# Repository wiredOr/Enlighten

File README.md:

# Arduino library to work with shift register-programmable LED lamps

## Supported LED lamps

* [PL9823](http://www.led-genial.de/mediafiles//Sonstiges/PL9823.pdf)
* [WS2812B](https://www.adafruit.com/datasheets/WS2812B.pdf)

## Build system requirements

* [Arduino](https://www.arduino.cc/en/Main/Software) (tested with v1.6.7)

## Reference

* [Arduino IDE 1.5: Library specification](https://github.com/arduino/Arduino/wiki/Arduino-IDE-1.5:-Library-specification)

## License

MIT style. See [here](./LICENSE).

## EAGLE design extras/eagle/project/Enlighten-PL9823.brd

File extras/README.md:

# Extras

Put documentation or other items to be bundled with the library here.

## CadSoft Eagle project

The folder "eagle" contains schematics, library and board files for the required hardware components, as well as ZIP archives containing pre-created Gerber files.

## Timing

The file "timing.txt" contains electrical and timing data, based on the datasheets of the PL9823 and WS2812-B shift register-programmable LED lamps.

## Bluetooth

This project uses the HC-05 Bluetooth module from Guangzhou HC Information Technology Co., Ltd., mounted on the so-called "gomcu" baseplate ("gomcu CZ-HC-05"). The folder "bluetooth" contains documentation about the HC-05 Bluetooth module.

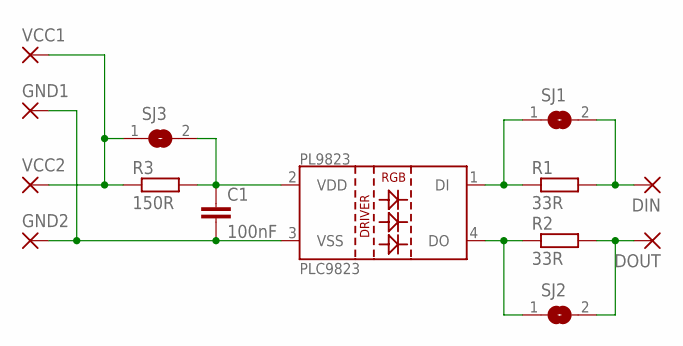
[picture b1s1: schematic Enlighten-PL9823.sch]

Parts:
C1: 100nF; C025-024X044
DIN: SMD2; SMD1,27-2,54
DOUT: SMD2; SMD1,27-2,54
GND1, GND2: SMD5; SMD2,54-5,08
PLC9823: LED-PL9823-F5W
R1, R2: 33R; 0207/10
R3: 150R; 0207/10
SJ1, SJ2, SJ3: SJ
VCC1, VCC2: SMD5; SMD2,54-5,08

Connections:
GND: C1.2, GND1.1, GND2.1, PLC9823.3 (VSS)
unnamed: PLC9823.1 (DI), R1.1, SJ1.1
unnamed: PLC9823.4 (DO), R2.1, SJ2.1
unnamed: DIN.1, R1.2, SJ1.2
unnamed: DOUT.1, R2.2, SJ2.2
unnamed: C1.1, PLC9823.2 (VDD), R3.2, SJ3.2
VCC: R3.1, SJ3.1, VCC1.1, VCC2.1

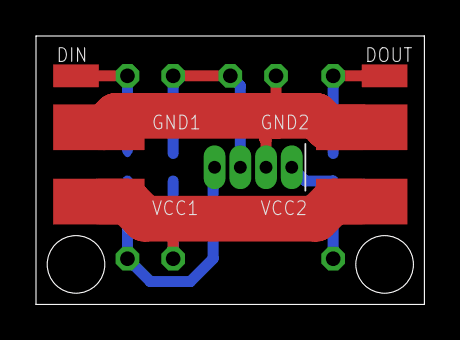
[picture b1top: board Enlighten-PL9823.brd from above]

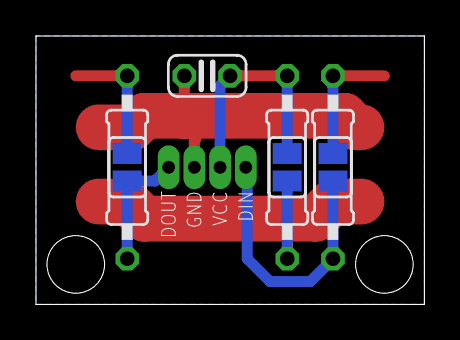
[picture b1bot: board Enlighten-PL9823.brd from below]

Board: 2 copper layers, 21.6 x 14.9 mm, 14 parts (7 on the bottom side), 7 nets.

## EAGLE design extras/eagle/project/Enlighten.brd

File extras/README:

Put documentation or other items to be bundled with the library here.

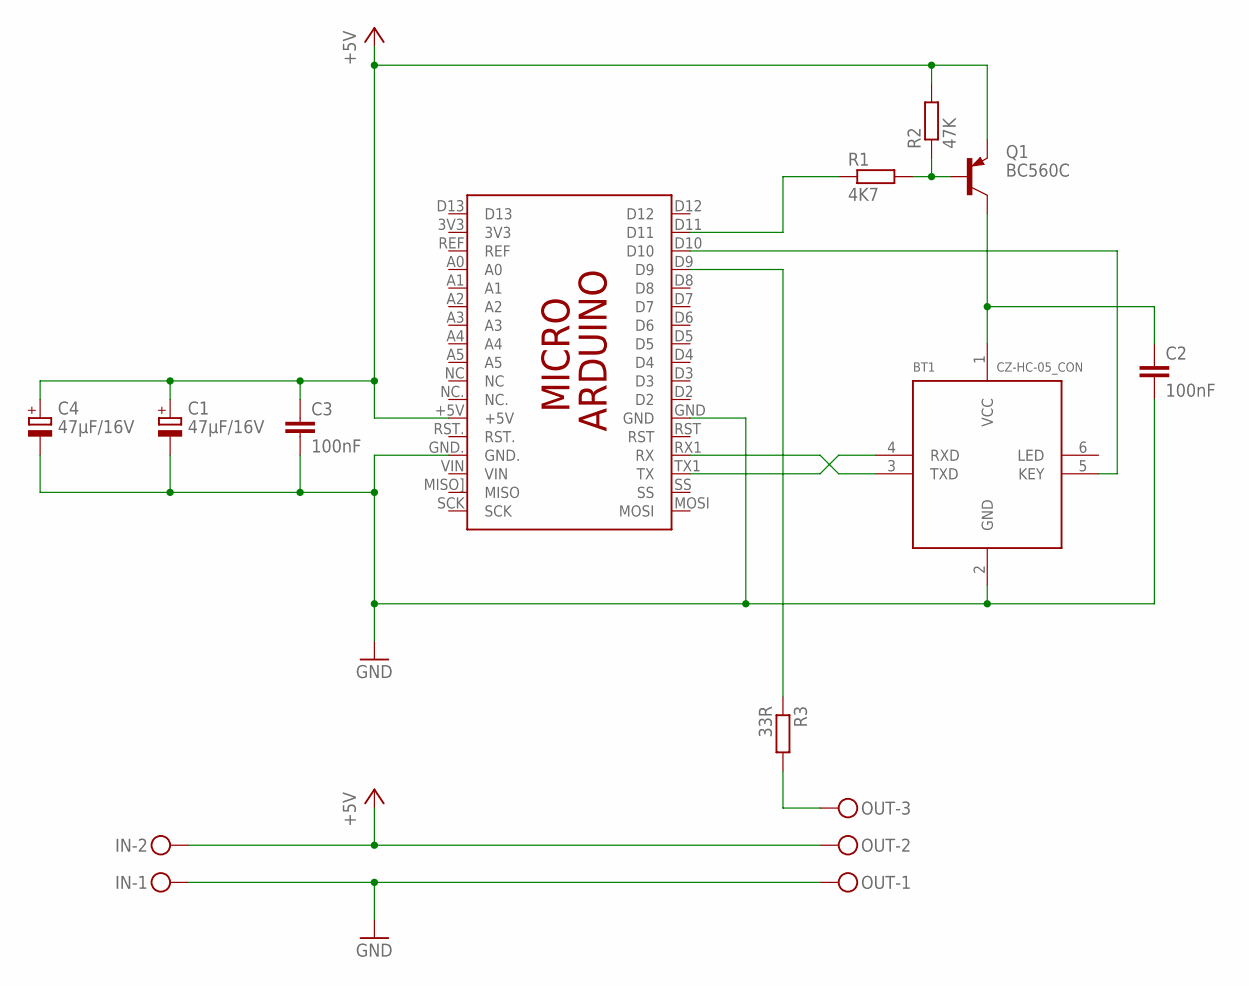
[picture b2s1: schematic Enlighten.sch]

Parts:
BT1: CZ-HC-05_CON
C1, C4: 47µF/16V; E2-5
C2, C3: 100nF; C050-024X044
IN: MKDSN1,5/2-5,08
OUT: MKDSN1,5/3-5,08
PCB1: ARDUINO_MICRO
Q1: BC560C; TO92-EBC
R1: 4K7; 0207/10
R2: 47K; 0207/10
R3: 33R; 0207/10

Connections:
+5V: C1.+, C3.1, C4.+, IN.2, OUT.2, PCB1.+5V, Q1.E, R2.2
BT_KEY: BT1.5 (KEY), PCB1.D10
BT_POWER: PCB1.D11, R1.1
BT_RX: BT1.4 (RXD), PCB1.TX1 (TX)
BT_TX: BT1.3 (TXD), PCB1.RX1 (RX)
DATA: OUT.3, R3.2
GND: BT1.2 (GND), C1.-, C2.2, C3.2, C4.-, IN.1, OUT.1, PCB1.GND, PCB1.GND.
unnamed: BT1.1 (VCC), C2.1, Q1.C
unnamed: Q1.B, R1.2, R2.1
unnamed: PCB1.D9, R3.1

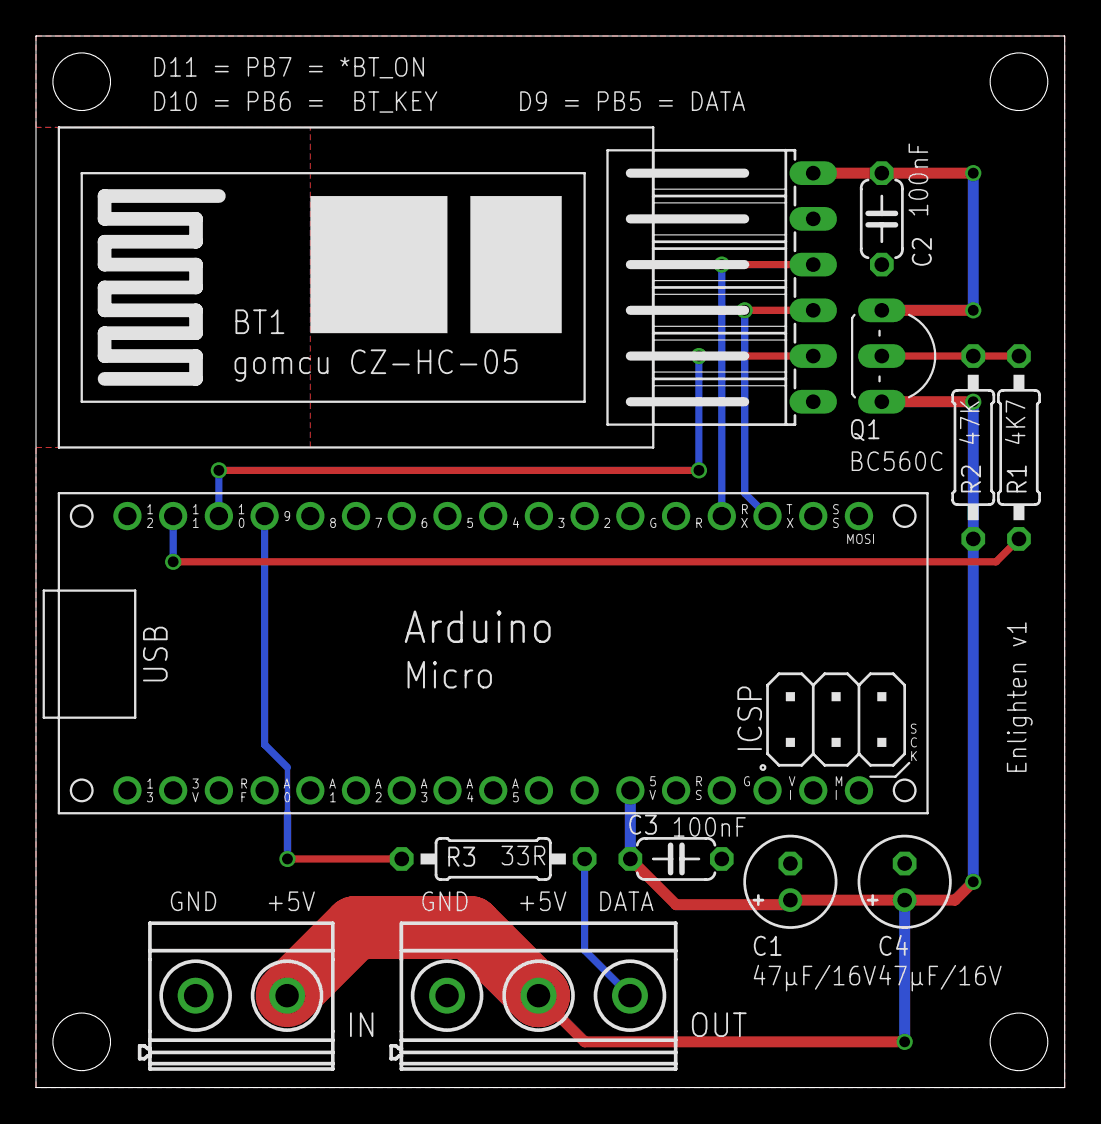
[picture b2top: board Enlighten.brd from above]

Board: 2 copper layers, 57.1 x 58.4 mm, 12 parts (0 on the bottom side), 10 nets.

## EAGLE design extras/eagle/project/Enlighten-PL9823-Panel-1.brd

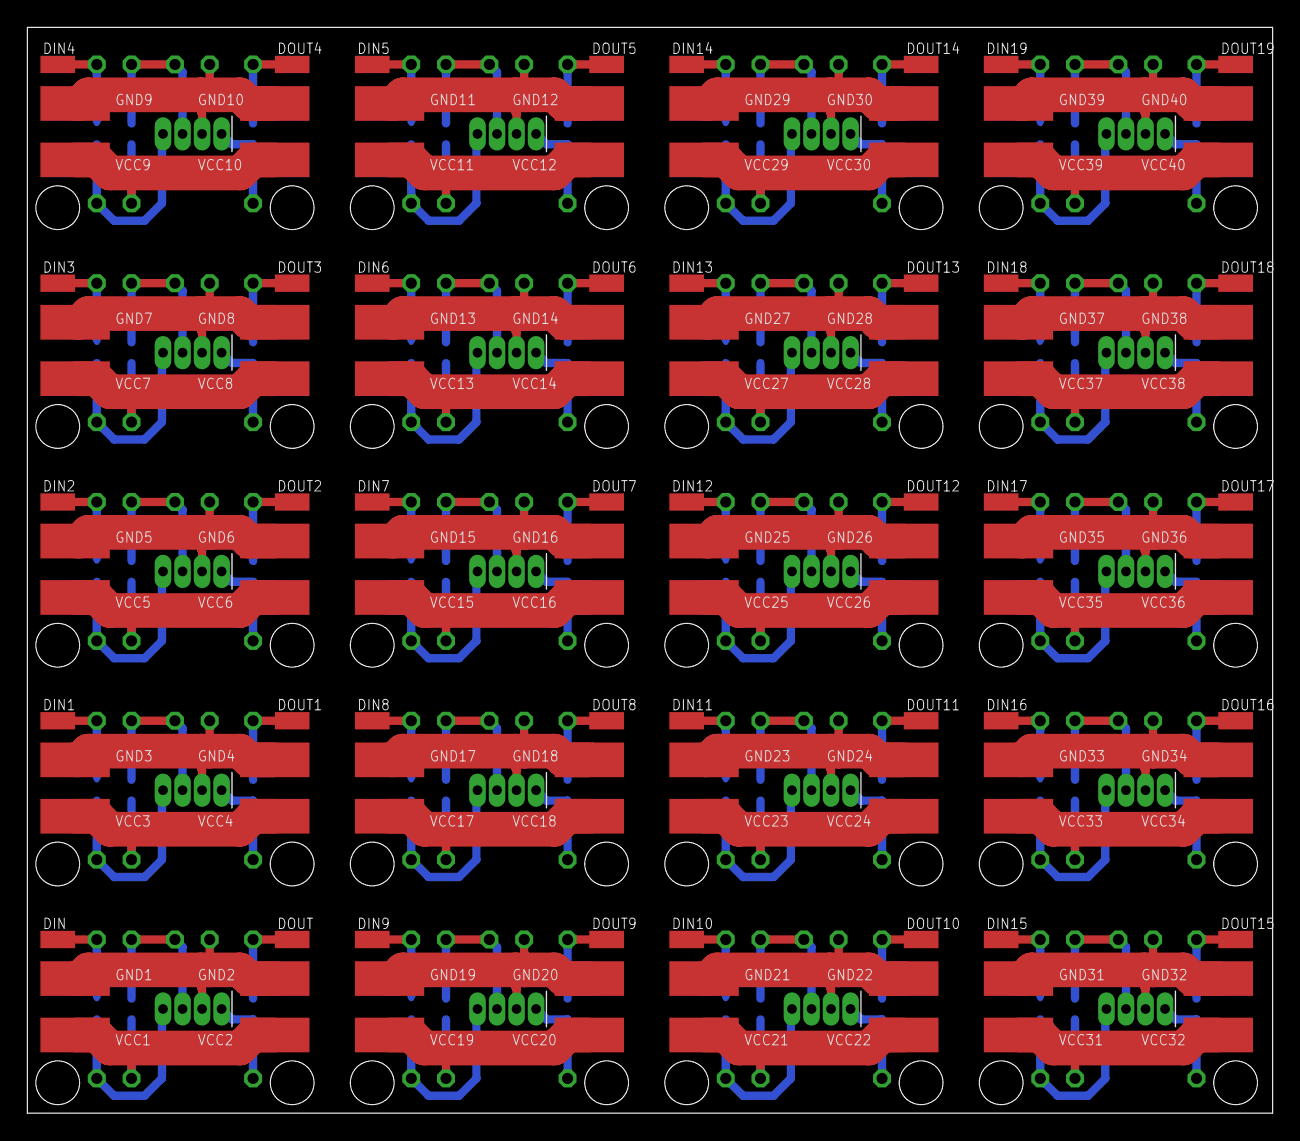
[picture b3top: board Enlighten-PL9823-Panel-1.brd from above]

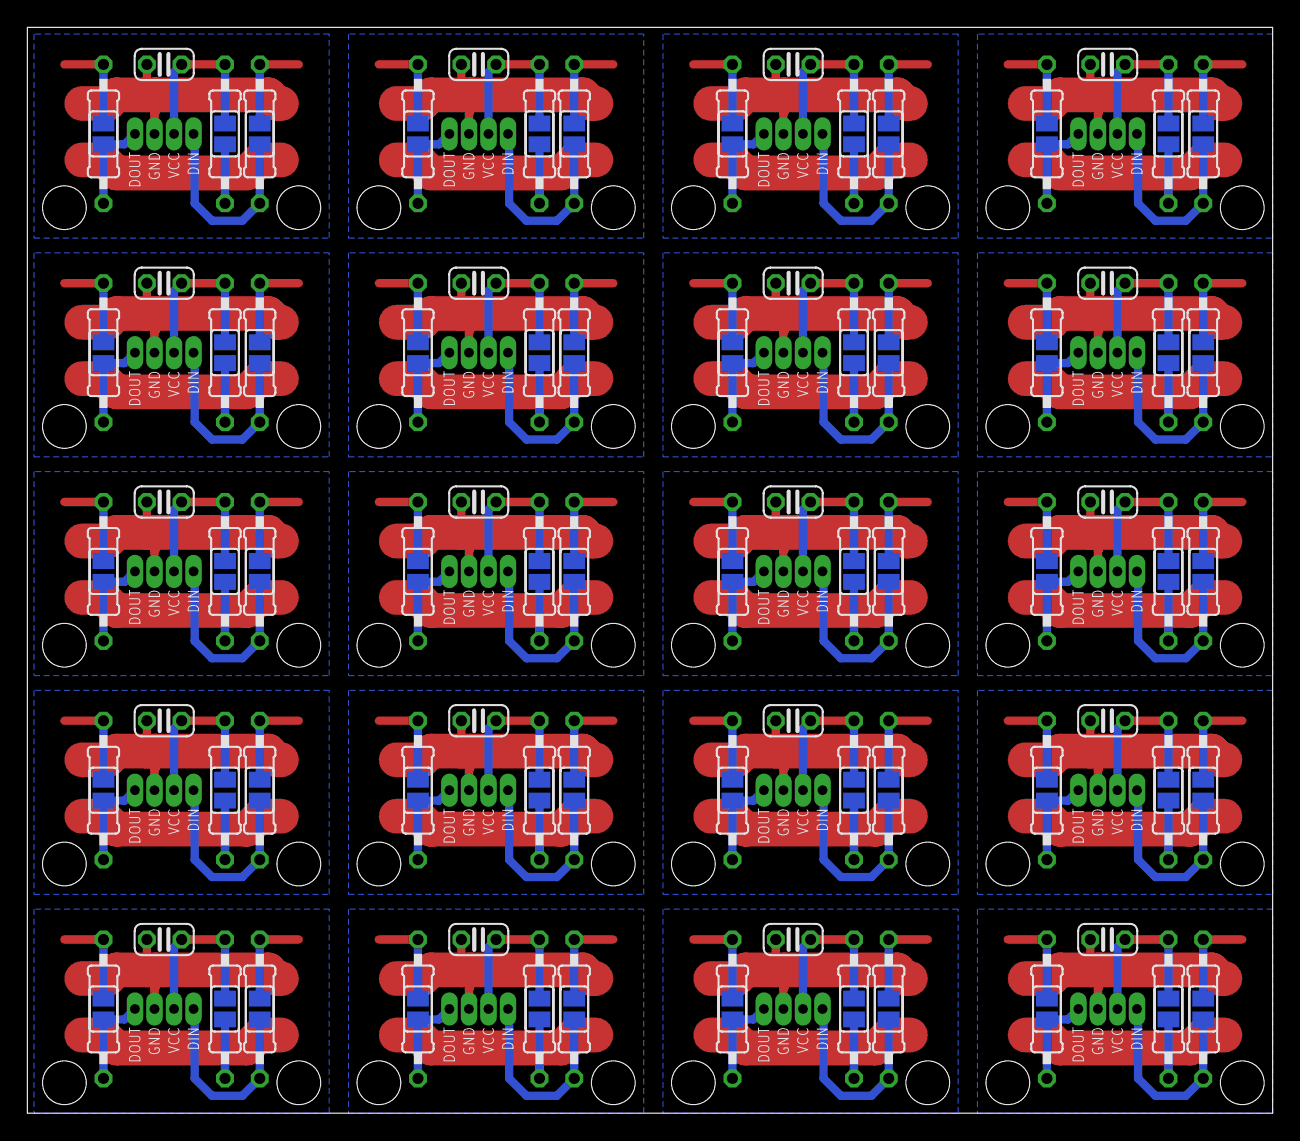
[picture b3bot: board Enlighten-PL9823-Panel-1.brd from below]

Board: 2 copper layers, 91.1 x 79.4 mm, 280 parts (140 on the bottom side), 140 nets.

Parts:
C1, C2, C3, C4, C5, C6, C7, C8, C9, C10, C11, C12, C13, C14, C15, C16, C17, C18, C19, C20: 100nF; C025-024X044
DIN, DIN1, DIN2, DIN3, DIN4, DIN5, DIN6, DIN7, DIN8, DIN9, DIN10, DIN11, DIN12, DIN13, DIN14, DIN15, DIN16, DIN17, DIN18, DIN19: SMD1,27-2,54
DOUT, DOUT1, DOUT2, DOUT3, DOUT4, DOUT5, DOUT6, DOUT7, DOUT8, DOUT9, DOUT10, DOUT11, DOUT12, DOUT13, DOUT14, DOUT15, DOUT16, DOUT17, DOUT18, DOUT19: SMD1,27-2,54
GND1, GND2, GND3, GND4, GND5, GND6, GND7, GND8, GND9, GND10, GND11, GND12, GND13, GND14, GND15, GND16, GND17, GND18, GND19, GND20, GND21, GND22, GND23, GND24, GND25, GND26, GND27, GND28, GND29, GND30, GND31, GND32, GND33, GND34, GND35, GND36, GND37, GND38, GND39, GND40: SMD2,54-5,08
PLC1, PLC2, PLC3, PLC4, PLC5, PLC6, PLC7, PLC8, PLC9, PLC10, PLC11, PLC12, PLC13, PLC14, PLC15, PLC16, PLC17, PLC18, PLC19, PLC9823: LED-PL9823-F5W
R1, R2, R4, R5, R7, R8, R10, R11, R13, R14, R16, R17, R19, R20, R22, R23, R25, R26, R28, R29, R31, R32, R34, R35, R37, R38, R40, R41, R43, R44, R46, R47, R49, R50, R52, R53, R55, R56, R58, R59: 33R; 0207/10
R3, R6, R9, R12, R15, R18, R21, R24, R27, R30, R33, R36, R39, R42, R45, R48, R51, R54, R57, R60: 150R; 0207/10
SJ1, SJ2, SJ3, SJ4, SJ5, SJ6, SJ7, SJ8, SJ9, SJ10, SJ11, SJ12, SJ13, SJ14, SJ15, SJ16, SJ17, SJ18, SJ19, SJ20, SJ21, SJ22, SJ23, SJ24, SJ25, SJ26, SJ27, SJ28, SJ29, SJ30, SJ31, SJ32, SJ33, SJ34, SJ35, SJ36, SJ37, SJ38, SJ39, SJ40, SJ41, SJ42, SJ43, SJ44, SJ45, SJ46, SJ47, SJ48, SJ49, SJ50, SJ51, SJ52, SJ53, SJ54, SJ55, SJ56, SJ57, SJ58, SJ59, SJ60: SJ
VCC1, VCC2, VCC3, VCC4, VCC5, VCC6, VCC7, VCC8, VCC9, VCC10, VCC11, VCC12, VCC13, VCC14, VCC15, VCC16, VCC17, VCC18, VCC19, VCC20, VCC21, VCC22, VCC23, VCC24, VCC25, VCC26, VCC27, VCC28, VCC29, VCC30, VCC31, VCC32, VCC33, VCC34, VCC35, VCC36, VCC37, VCC38, VCC39, VCC40: SMD2,54-5,08

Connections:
GND: C1.2, GND1.1, GND2.1, PLC9823.3
GND1: C2.2, GND3.1, GND4.1, PLC1.3
GND2: C3.2, GND5.1, GND6.1, PLC2.3
GND3: C4.2, GND7.1, GND8.1, PLC3.3
GND4: C5.2, GND9.1, GND10.1, PLC4.3
GND5: C6.2, GND11.1, GND12.1, PLC5.3
GND6: C7.2, GND13.1, GND14.1, PLC6.3
GND7: C8.2, GND15.1, GND16.1, PLC7.3
GND8: C9.2, GND17.1, GND18.1, PLC8.3
GND9: C10.2, GND19.1, GND20.1, PLC9.3
GND10: C11.2, GND21.1, GND22.1, PLC10.3
GND11: C12.2, GND23.1, GND24.1, PLC11.3
GND12: C13.2, GND25.1, GND26.1, PLC12.3
GND13: C14.2, GND27.1, GND28.1, PLC13.3
GND14: C15.2, GND29.1, GND30.1, PLC14.3
GND15: C16.2, GND31.1, GND32.1, PLC15.3
GND16: C17.2, GND33.1, GND34.1, PLC16.3
GND17: C18.2, GND35.1, GND36.1, PLC17.3
GND18: C19.2, GND37.1, GND38.1, PLC18.3
GND19: C20.2, GND39.1, GND40.1, PLC19.3
unnamed: PLC9823.1, R1.1, SJ1.1
unnamed: PLC9823.4, R2.1, SJ2.1
unnamed: DIN.1, R1.2, SJ1.2
unnamed: DOUT.1, R2.2, SJ2.2
unnamed: C1.1, PLC9823.2, R3.2, SJ3.2
unnamed: PLC1.1, R4.1, SJ4.1
unnamed: PLC1.4, R5.1, SJ5.1
unnamed: DIN1.1, R4.2, SJ4.2
unnamed: DOUT1.1, R5.2, SJ5.2
unnamed: C2.1, PLC1.2, R6.2, SJ6.2
unnamed: PLC2.1, R7.1, SJ7.1
unnamed: PLC2.4, R8.1, SJ8.1
unnamed: DIN2.1, R7.2, SJ7.2
unnamed: DOUT2.1, R8.2, SJ8.2
unnamed: C3.1, PLC2.2, R9.2, SJ9.2
unnamed: PLC3.1, R10.1, SJ10.1
unnamed: PLC3.4, R11.1, SJ11.1
unnamed: DIN3.1, R10.2, SJ10.2
unnamed: DOUT3.1, R11.2, SJ11.2
unnamed: C4.1, PLC3.2, R12.2, SJ12.2
unnamed: PLC4.1, R13.1, SJ13.1
unnamed: PLC4.4, R14.1, SJ14.1
unnamed: DIN4.1, R13.2, SJ13.2
unnamed: DOUT4.1, R14.2, SJ14.2
unnamed: C5.1, PLC4.2, R15.2, SJ15.2
unnamed: PLC5.1, R16.1, SJ16.1
unnamed: PLC5.4, R17.1, SJ17.1
unnamed: DIN5.1, R16.2, SJ16.2
unnamed: DOUT5.1, R17.2, SJ17.2
unnamed: C6.1, PLC5.2, R18.2, SJ18.2
unnamed: PLC6.1, R19.1, SJ19.1
unnamed: PLC6.4, R20.1, SJ20.1
unnamed: DIN6.1, R19.2, SJ19.2
unnamed: DOUT6.1, R20.2, SJ20.2
unnamed: C7.1, PLC6.2, R21.2, SJ21.2
unnamed: PLC7.1, R22.1, SJ22.1
unnamed: PLC7.4, R23.1, SJ23.1
unnamed: DIN7.1, R22.2, SJ22.2
unnamed: DOUT7.1, R23.2, SJ23.2
unnamed: C8.1, PLC7.2, R24.2, SJ24.2
unnamed: PLC8.1, R25.1, SJ25.1
unnamed: PLC8.4, R26.1, SJ26.1
unnamed: DIN8.1, R25.2, SJ25.2
unnamed: DOUT8.1, R26.2, SJ26.2
unnamed: C9.1, PLC8.2, R27.2, SJ27.2
unnamed: PLC9.1, R28.1, SJ28.1
unnamed: PLC9.4, R29.1, SJ29.1
unnamed: DIN9.1, R28.2, SJ28.2
unnamed: DOUT9.1, R29.2, SJ29.2
unnamed: C10.1, PLC9.2, R30.2, SJ30.2
unnamed: PLC10.1, R31.1, SJ31.1
unnamed: PLC10.4, R32.1, SJ32.1
unnamed: DIN10.1, R31.2, SJ31.2
unnamed: DOUT10.1, R32.2, SJ32.2
unnamed: C11.1, PLC10.2, R33.2, SJ33.2
unnamed: PLC11.1, R34.1, SJ34.1
unnamed: PLC11.4, R35.1, SJ35.1
unnamed: DIN11.1, R34.2, SJ34.2
unnamed: DOUT11.1, R35.2, SJ35.2
unnamed: C12.1, PLC11.2, R36.2, SJ36.2
unnamed: PLC12.1, R37.1, SJ37.1
unnamed: PLC12.4, R38.1, SJ38.1
unnamed: DIN12.1, R37.2, SJ37.2
unnamed: DOUT12.1, R38.2, SJ38.2
unnamed: C13.1, PLC12.2, R39.2, SJ39.2
unnamed: PLC13.1, R40.1, SJ40.1
unnamed: PLC13.4, R41.1, SJ41.1
unnamed: DIN13.1, R40.2, SJ40.2
unnamed: DOUT13.1, R41.2, SJ41.2
unnamed: C14.1, PLC13.2, R42.2, SJ42.2
unnamed: PLC14.1, R43.1, SJ43.1
unnamed: PLC14.4, R44.1, SJ44.1
unnamed: DIN14.1, R43.2, SJ43.2
unnamed: DOUT14.1, R44.2, SJ44.2
unnamed: C15.1, PLC14.2, R45.2, SJ45.2
unnamed: PLC15.1, R46.1, SJ46.1
unnamed: PLC15.4, R47.1, SJ47.1
unnamed: DIN15.1, R46.2, SJ46.2
unnamed: DOUT15.1, R47.2, SJ47.2
unnamed: C16.1, PLC15.2, R48.2, SJ48.2
unnamed: PLC16.1, R49.1, SJ49.1
unnamed: PLC16.4, R50.1, SJ50.1
unnamed: DIN16.1, R49.2, SJ49.2
unnamed: DOUT16.1, R50.2, SJ50.2
unnamed: C17.1, PLC16.2, R51.2, SJ51.2
unnamed: PLC17.1, R52.1, SJ52.1
unnamed: PLC17.4, R53.1, SJ53.1
unnamed: DIN17.1, R52.2, SJ52.2
unnamed: DOUT17.1, R53.2, SJ53.2
unnamed: C18.1, PLC17.2, R54.2, SJ54.2
unnamed: PLC18.1, R55.1, SJ55.1
unnamed: PLC18.4, R56.1, SJ56.1
unnamed: DIN18.1, R55.2, SJ55.2
unnamed: DOUT18.1, R56.2, SJ56.2
unnamed: C19.1, PLC18.2, R57.2, SJ57.2
unnamed: PLC19.1, R58.1, SJ58.1
unnamed: PLC19.4, R59.1, SJ59.1
unnamed: DIN19.1, R58.2, SJ58.2
unnamed: DOUT19.1, R59.2, SJ59.2
unnamed: C20.1, PLC19.2, R60.2, SJ60.2
VCC: R3.1, SJ3.1, VCC1.1, VCC2.1
VCC1: R6.1, SJ6.1, VCC3.1, VCC4.1
VCC2: R9.1, SJ9.1, VCC5.1, VCC6.1
VCC3: R12.1, SJ12.1, VCC7.1, VCC8.1
VCC4: R15.1, SJ15.1, VCC9.1, VCC10.1
VCC5: R18.1, SJ18.1, VCC11.1, VCC12.1
VCC6: R21.1, SJ21.1, VCC13.1, VCC14.1
VCC7: R24.1, SJ24.1, VCC15.1, VCC16.1
VCC8: R27.1, SJ27.1, VCC17.1, VCC18.1
VCC9: R30.1, SJ30.1, VCC19.1, VCC20.1
VCC10: R33.1, SJ33.1, VCC21.1, VCC22.1
VCC11: R36.1, SJ36.1, VCC23.1, VCC24.1
VCC12: R39.1, SJ39.1, VCC25.1, VCC26.1
VCC13: R42.1, SJ42.1, VCC27.1, VCC28.1
VCC14: R45.1, SJ45.1, VCC29.1, VCC30.1
VCC15: R48.1, SJ48.1, VCC31.1, VCC32.1
VCC16: R51.1, SJ51.1, VCC33.1, VCC34.1
VCC17: R54.1, SJ54.1, VCC35.1, VCC36.1
VCC18: R57.1, SJ57.1, VCC37.1, VCC38.1
VCC19: R60.1, SJ60.1, VCC39.1, VCC40.1

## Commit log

2016-01-04 First blood
2016-01-06 Use default values for AVR target MCU selection
2016-01-07 Remove Eclipse project nature. Too many obstacles to develop an Arduino library using Eclipse+CDT+AVR-GCC.
2016-01-07 Add example sketch
2016-02-15 Remove Eclipse project files
2016-02-15 Fix .gitignore
2016-02-15 Add CadSoft Eagle project and LED timing documentation
2016-02-15 Documentation update
2016-02-15 Add Bluetooth module documentation
2016-02-23 Add EnlightenBT class to control the bluetooth module
2016-02-24 Some more serial mangling
2016-02-27 Lots of improvements for BT module command handling; Fix BT module on/off settle timing
2016-03-16 Abstract LED chain
2016-03-16 Add LED dottiest
2016-03-16 Start PL9823-specific implementation
2016-03-17 Finish first version of led array flinging for PL9823
2016-03-17 Fis: delay loop runs for too long
2016-03-17 First fling tests positive with PL9823; Bug fixes; Fix compiler warnings; Next example LedChain.ino
2016-03-18 More work on the LED chain API; Bug fixes; More extensive fling testing - looks good!
2016-04-05 Fix bugs; Implementation for WS2812B is code complete, but untested yet
2016-04-06 Confirmed working for WS2812B; Comment fix
2016-04-06 Comments; Added copyBuffer()
2016-04-08 Add some more pixel setter methods
2016-04-08 Rewrite implementation classes using templates to reduce code and keep performance
2016-04-22 Add some more HC-06 relevant data sheets
2016-05-02 Reduced code by eliminating dynamic implementations.
